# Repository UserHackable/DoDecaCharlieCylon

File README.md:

## DoDecaCharlieCylon 

### Board dimensions

* (157451, 79961) original units
* (1.5745, 0.7996) inches
* (39.9926, 20.3101) mm

| Front | Back |
| --- | --- |
|  |  |

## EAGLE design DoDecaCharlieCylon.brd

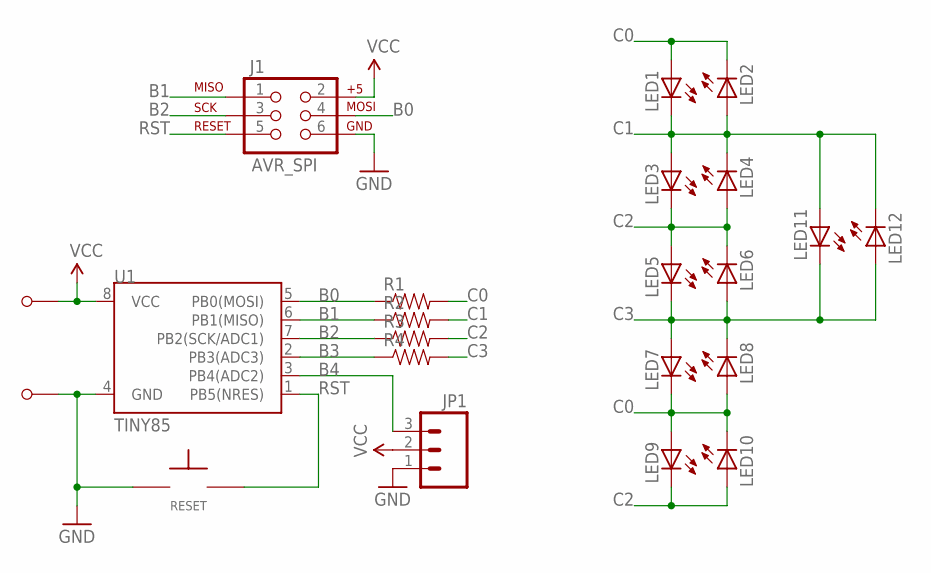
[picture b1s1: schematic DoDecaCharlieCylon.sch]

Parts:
J1: AVR_SPI; 2X3-NS
JP1: M03PTH; 1X03
LED1, LED2, LED3, LED4, LED5, LED6, LED7, LED8, LED9, LED10, LED11, LED12: LEDOVAL; LED-OVAL
R1, R2, R3, R4: RESISTORAXIAL-0.3; AXIAL-0.3
RESET: TAC_SPST_NO
U1: TINY85; DIP08
U$1, U$2: M1; M1_NO_STRAIN

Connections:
B0: J1.4 (MOSI), R1.P$1 (1), U1.5 (PB0(MOSI))
B1: J1.1 (MISO), R2.P$1 (1), U1.6 (PB1(MISO))
B2: J1.3 (SCK), R3.P$1 (1), U1.7 (PB2(SCK/ADC1))
B3: R4.P$1 (1), U1.2 (PB3(ADC3))
B4: JP1.3, U1.3 (PB4(ADC2))
C0: LED1.ANODE (A), LED2.CATHODE (C), LED7.CATHODE (C), LED8.ANODE (A), LED9.ANODE (A), LED10.CATHODE (C), R1.P$2 (2)
C1: LED1.CATHODE (C), LED2.ANODE (A), LED3.ANODE (A), LED4.CATHODE (C), LED11.ANODE (A), LED12.CATHODE (C), R2.P$2 (2)
C2: LED3.CATHODE (C), LED4.ANODE (A), LED5.ANODE (A), LED6.CATHODE (C), LED9.CATHODE (C), LED10.ANODE (A), R3.P$2 (2)
C3: LED5.CATHODE (C), LED6.ANODE (A), LED7.ANODE (A), LED8.CATHODE (C), LED11.CATHODE (C), LED12.ANODE (A), R4.P$2 (2)
GND: J1.6 (GND), JP1.1, RESET.P$1, U1.4 (GND), U$2.P$1
RST: J1.5 (RST), RESET.P$2, U1.1 (PB5(NRES))
VCC: J1.2 (V+), JP1.2, U1.8 (VCC), U$1.P$1

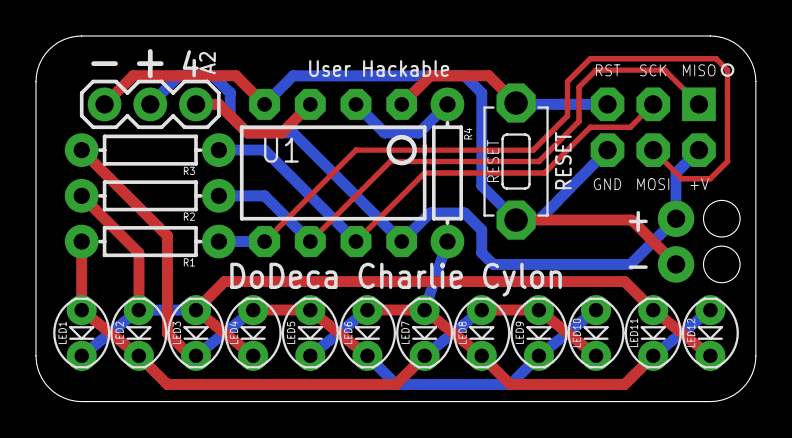
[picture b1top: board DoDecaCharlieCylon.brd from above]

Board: 2 copper layers, 40.0 x 20.3 mm, 22 parts (0 on the bottom side), 12 nets.

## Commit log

2016-04-07 from Makefile

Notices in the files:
parts and their libraries:
SparkFun-DigitalIC: Licensing: Creative Commons ShareAlike 4.0 International - https://creativecommons.org/licenses/by-sa/4.0
